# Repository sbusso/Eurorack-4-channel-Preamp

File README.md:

# Eurorack-4-channel-Preamp
A simple 4 channel Eurorack preamp. Each Channel is independent.
It includes files for home etching, 2 sided boards.

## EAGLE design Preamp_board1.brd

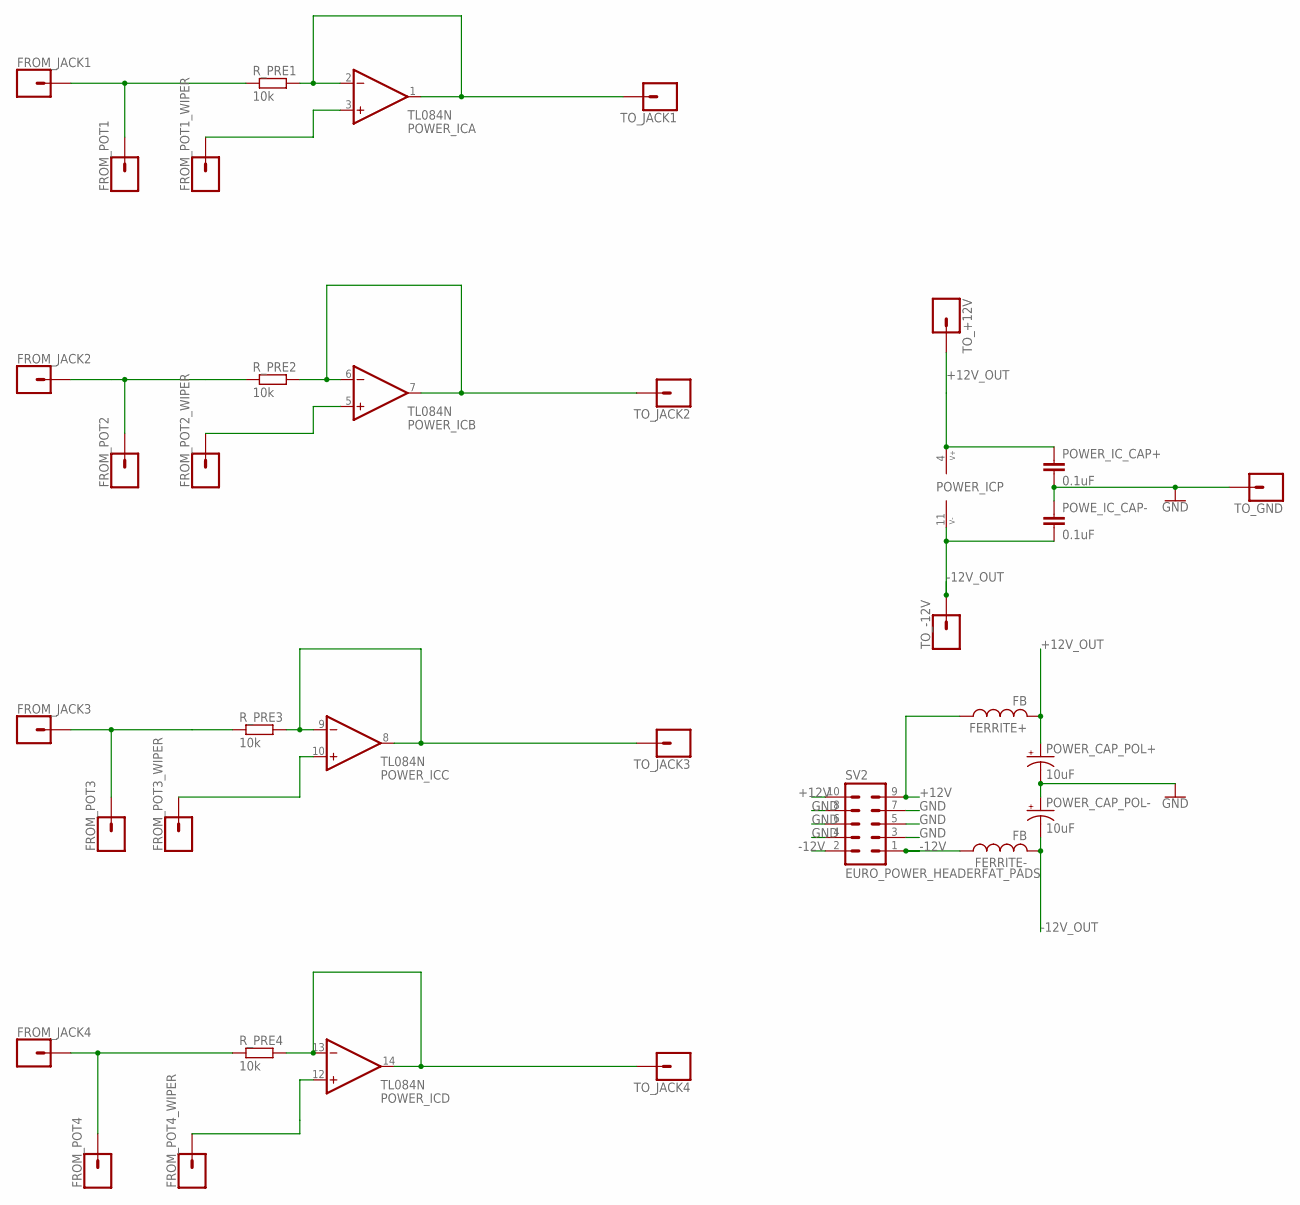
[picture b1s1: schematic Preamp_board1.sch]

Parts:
FERRITE+: FB
FERRITE-: FB
FROM_JACK1, FROM_JACK2, FROM_JACK3, FROM_JACK4: CONN_01PTH_LONGPAD; 1X01_LONGPAD
FROM_POT1, FROM_POT1_WIPER, FROM_POT2, FROM_POT2_WIPER, FROM_POT3, FROM_POT3_WIPER, FROM_POT4, FROM_POT4_WIPER: CONN_01PTH_LONGPAD; 1X01_LONGPAD
POWER_CAP_POL+: 10uF; CPOL-RADIAL-2.5MM-5MM
POWER_CAP_POL-: 10uF; CPOL-RADIAL-2.5MM-5MM
POWER_IC: TL084N; DIL14
POWER_IC_CAP+: 0.1uF; CAP-PTH-SMALL-KIT
POWE_IC_CAP-: 0.1uF; CAP-PTH-SMALL-KIT
R_PRE1, R_PRE2, R_PRE3, R_PRE4: 10k; 7MM_RESISTOR
SV2: EURO_POWER_HEADERFAT_PADS; EURO_PWR_HEADER_FAT
TO_+12V: CONN_01PTH_LONGPAD; 1X01_LONGPAD
TO_-12V: CONN_01PTH_LONGPAD; 1X01_LONGPAD
TO_GND: CONN_01PTH_LONGPAD; 1X01_LONGPAD
TO_JACK1, TO_JACK2, TO_JACK3, TO_JACK4: CONN_01PTH_LONGPAD; 1X01_LONGPAD

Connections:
+12V: FERRITE+.P$1 (1), SV2.9, SV2.10
+12V_OUT: FERRITE+.P$2 (2), POWER_CAP_POL+.1 (+), POWER_IC.4 (V+), POWER_IC_CAP+.1, TO_+12V.1
-12V: FERRITE-.P$1 (1), SV2.1, SV2.2
-12V_OUT: FERRITE-.P$2 (2), POWER_CAP_POL-.2 (-), POWER_IC.11 (V-), POWE_IC_CAP-.2, TO_-12V.1
GND: POWER_CAP_POL+.2 (-), POWER_CAP_POL-.1 (+), POWER_IC_CAP+.2, POWE_IC_CAP-.1, SV2.3, SV2.4, SV2.5, SV2.6, SV2.7, SV2.8, TO_GND.1
unnamed: POWER_IC.13 (-IN), POWER_IC.14 (OUT), R_PRE4.2, TO_JACK4.1
unnamed: FROM_JACK3.1, FROM_POT3.1, R_PRE3.1
unnamed: FROM_JACK1.1, FROM_POT1.1, R_PRE1.1
unnamed: POWER_IC.1 (OUT), POWER_IC.2 (-IN), R_PRE1.2, TO_JACK1.1
unnamed: POWER_IC.6 (-IN), POWER_IC.7 (OUT), R_PRE2.2, TO_JACK2.1
unnamed: FROM_JACK2.1, FROM_POT2.1, R_PRE2.1
unnamed: FROM_JACK4.1, FROM_POT4.1, R_PRE4.1
unnamed: FROM_POT1_WIPER.1, POWER_IC.3 (+IN)
unnamed: FROM_POT2_WIPER.1, POWER_IC.5 (+IN)
unnamed: FROM_POT3_WIPER.1, POWER_IC.10 (+IN)
unnamed: FROM_POT4_WIPER.1, POWER_IC.12 (+IN)
unnamed: POWER_IC.8 (OUT), POWER_IC.9 (-IN), R_PRE3.2, TO_JACK3.1

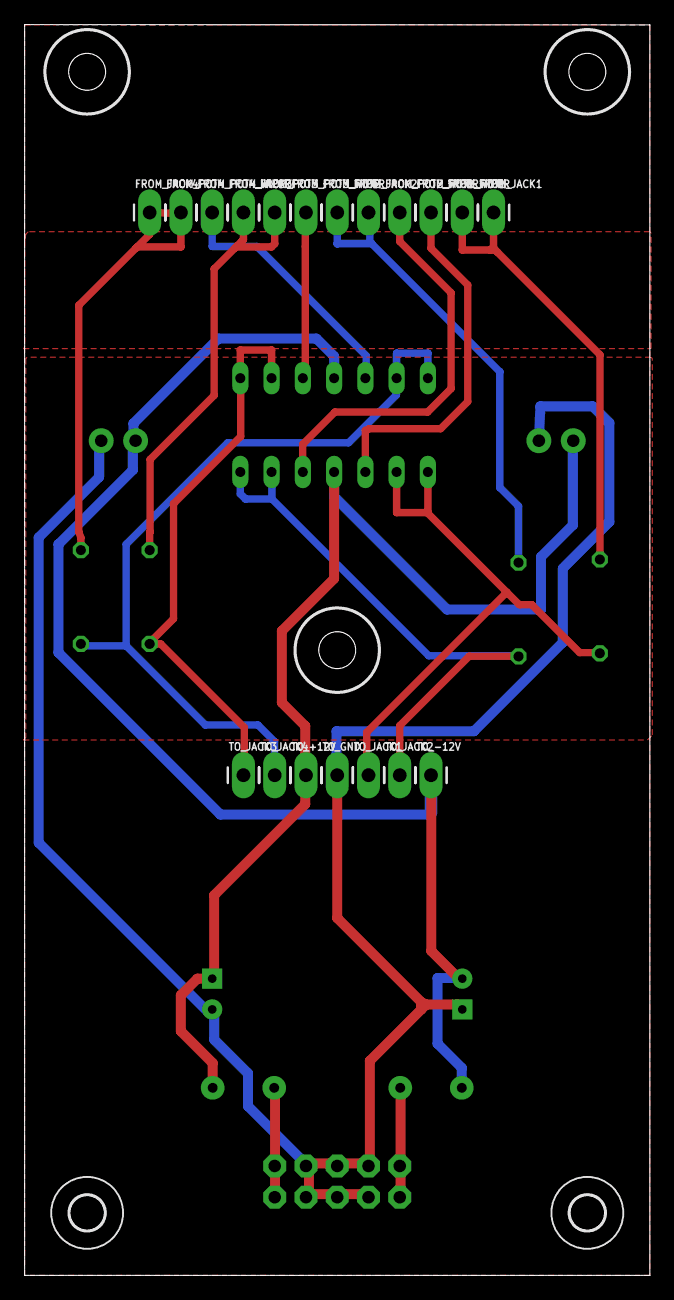
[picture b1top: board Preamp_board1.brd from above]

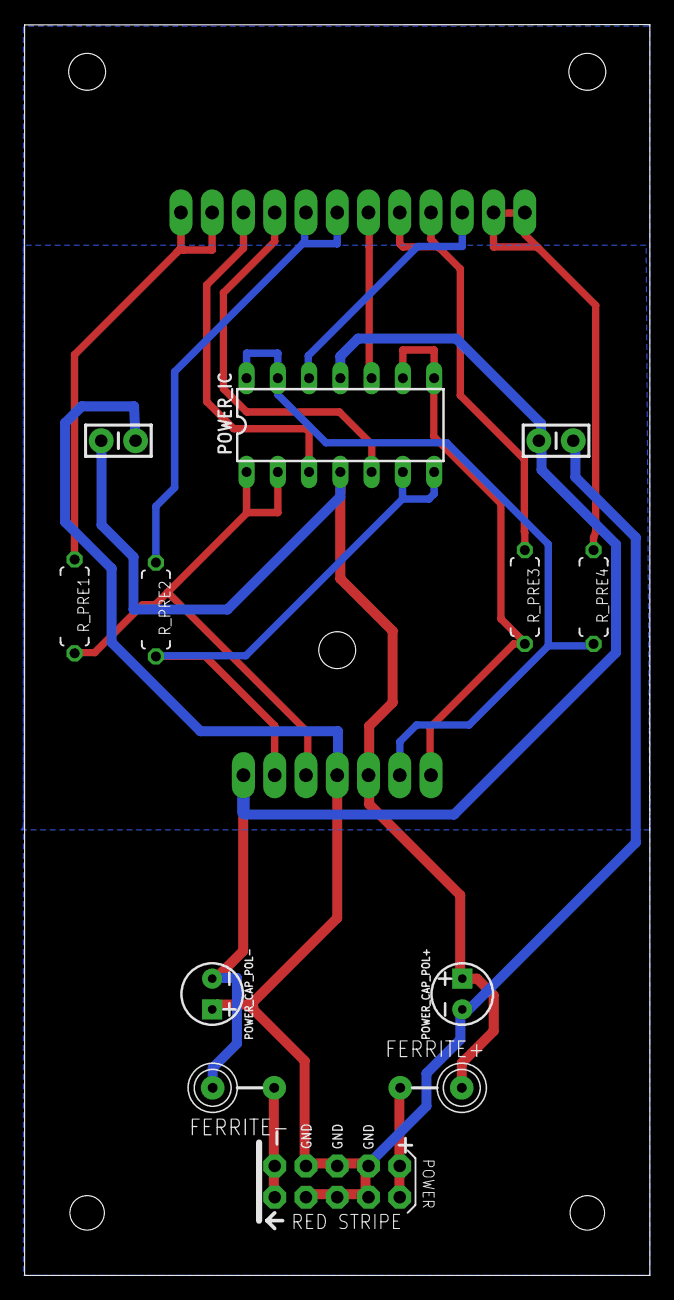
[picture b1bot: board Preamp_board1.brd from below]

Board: 2 copper layers, 50.8 x 101.6 mm, 36 parts (12 on the bottom side), 17 nets.

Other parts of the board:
H1, H2, H4: DRIL-3
U$1, U$2: 2,8

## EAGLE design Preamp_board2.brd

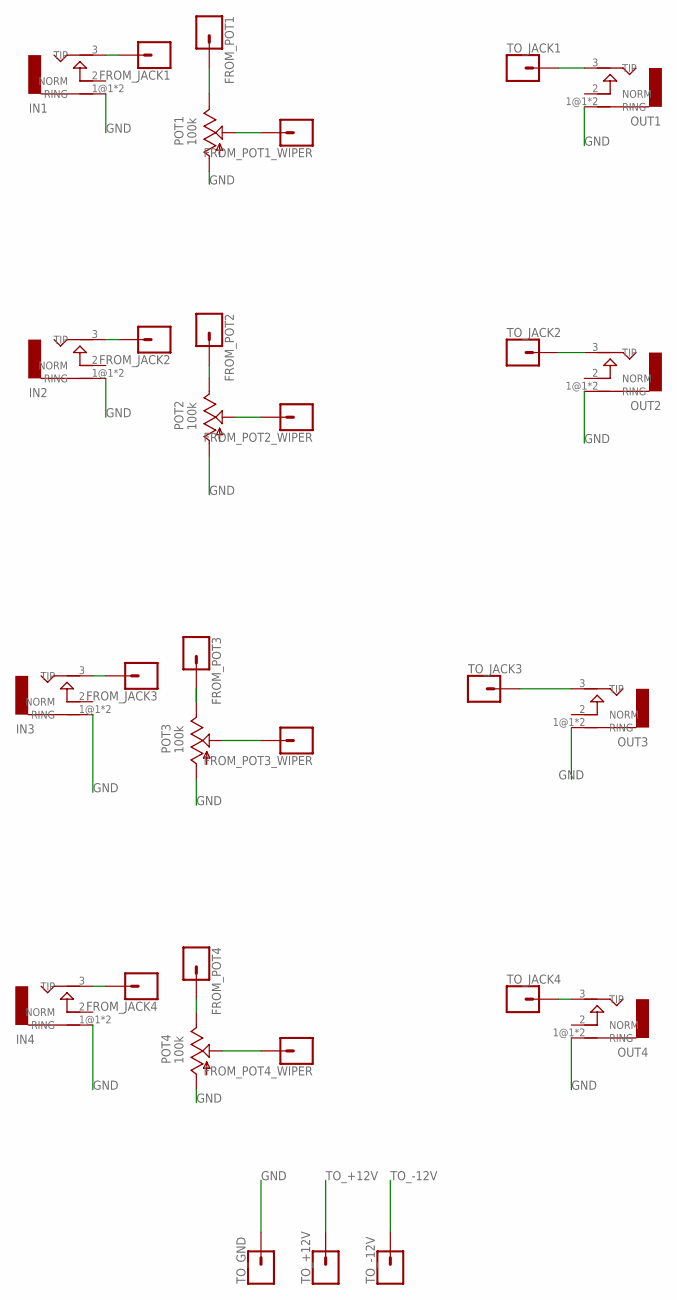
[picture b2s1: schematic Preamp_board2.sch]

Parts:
FROM_JACK1, FROM_JACK2, FROM_JACK3, FROM_JACK4: CONN_01PTH_LONGPAD; 1X01_LONGPAD
FROM_POT1, FROM_POT1_WIPER, FROM_POT2, FROM_POT2_WIPER, FROM_POT3, FROM_POT3_WIPER, FROM_POT4, FROM_POT4_WIPER: CONN_01PTH_LONGPAD; 1X01_LONGPAD
IN1, IN2, IN3, IN4: AUDIO-JACKERTHENVAR; ERTHENVAR-JACK
OUT1, OUT2, OUT3, OUT4: AUDIO-JACKERTHENVAR; ERTHENVAR-JACK
POT1, POT2, POT3, POT4: 100k; 9MM_SNAP-IN_POT
TO_+12V: CONN_01PTH_LONGPAD; 1X01_LONGPAD
TO_-12V: CONN_01PTH_LONGPAD; 1X01_LONGPAD
TO_GND: CONN_01PTH_LONGPAD; 1X01_LONGPAD
TO_JACK1, TO_JACK2, TO_JACK3, TO_JACK4: CONN_01PTH_LONGPAD; 1X01_LONGPAD

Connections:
GND: IN1.1@1 (RING), IN1.1@2 (RING), IN2.1@1 (RING), IN2.1@2 (RING), IN3.1@1 (RING), IN3.1@2 (RING), IN4.1@1 (RING), IN4.1@2 (RING), OUT1.1@1 (RING), OUT1.1@2 (RING), OUT2.1@1 (RING), OUT2.1@2 (RING), OUT3.1@1 (RING), OUT3.1@2 (RING), OUT4.1@1 (RING), OUT4.1@2 (RING), POT1.1 (A), POT2.1 (A), POT3.1 (A), POT4.1 (A), TO_GND.1
unnamed: OUT1.3 (TIP), TO_JACK1.1
unnamed: OUT2.3 (TIP), TO_JACK2.1
unnamed: OUT3.3 (TIP), TO_JACK3.1
unnamed: OUT4.3 (TIP), TO_JACK4.1
unnamed: FROM_POT4.1, POT4.3 (E)
unnamed: FROM_JACK1.1, IN1.3 (TIP)
unnamed: FROM_POT2.1, POT2.3 (E)
unnamed: FROM_JACK2.1, IN2.3 (TIP)
unnamed: FROM_POT1.1, POT1.3 (E)
unnamed: FROM_POT2_WIPER.1, POT2.2 (S)
unnamed: FROM_POT3_WIPER.1, POT3.2 (S)
unnamed: FROM_POT3.1, POT3.3 (E)
unnamed: FROM_JACK3.1, IN3.3 (TIP)
unnamed: FROM_POT4_WIPER.1, POT4.2 (S)
unnamed: FROM_JACK4.1, IN4.3 (TIP)
unnamed: FROM_POT1_WIPER.1, POT1.2 (S)
TO_+12V: TO_+12V.1
TO_-12V: TO_-12V.1

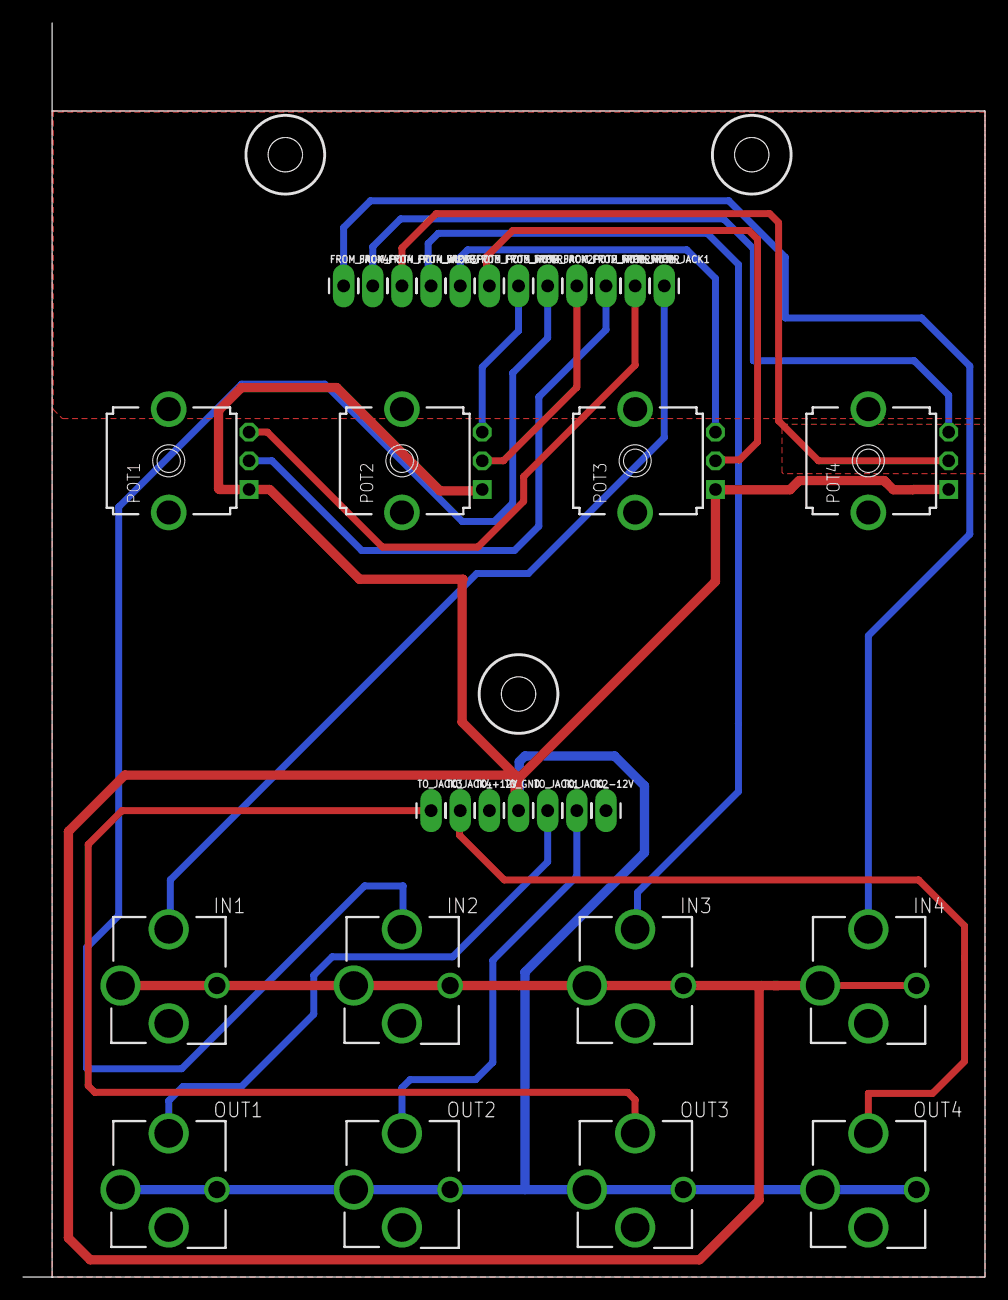
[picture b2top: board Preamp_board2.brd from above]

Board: 2 copper layers, 83.8 x 109.3 mm, 34 parts (0 on the bottom side), 17 nets.

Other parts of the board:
H1, H2, H5: DRIL-3

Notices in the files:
parts and their libraries:
SparkFun-Connectors: Licensing: Creative Commons ShareAlike 4.0 International - https://creativecommons.org/licenses/by-sa/4.0
op-amp: Copyright (C) 2006 by Bob Starr
